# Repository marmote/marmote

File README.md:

Marmote is a National Science Foundation supported collaborative research project between Vanderbilt University and the University of Michigan. The goal of the project is to create a novel low-power experimental platform for wireless networking research and education.

The proposed Marmote platform breaks with the prevailing approach to wireless sensor network (WSN) hardware, which combines a general purpose microcontroller with a highly integrated radio transceiver, and places a flash-based Field Programmable Gate Array (FPGA) along with a flexible Analog Front-End (AFE) in the center to become:
 
 - low-power
 - powerful
 - flexible
 - modular
 
The above approach allows for interfacing and experimenting with different type of sensors including analog radio front-ends. In contrast with the "traditional" integrated radio chip solution this enables access to the physical layer and, hence, to baseband firmware development.

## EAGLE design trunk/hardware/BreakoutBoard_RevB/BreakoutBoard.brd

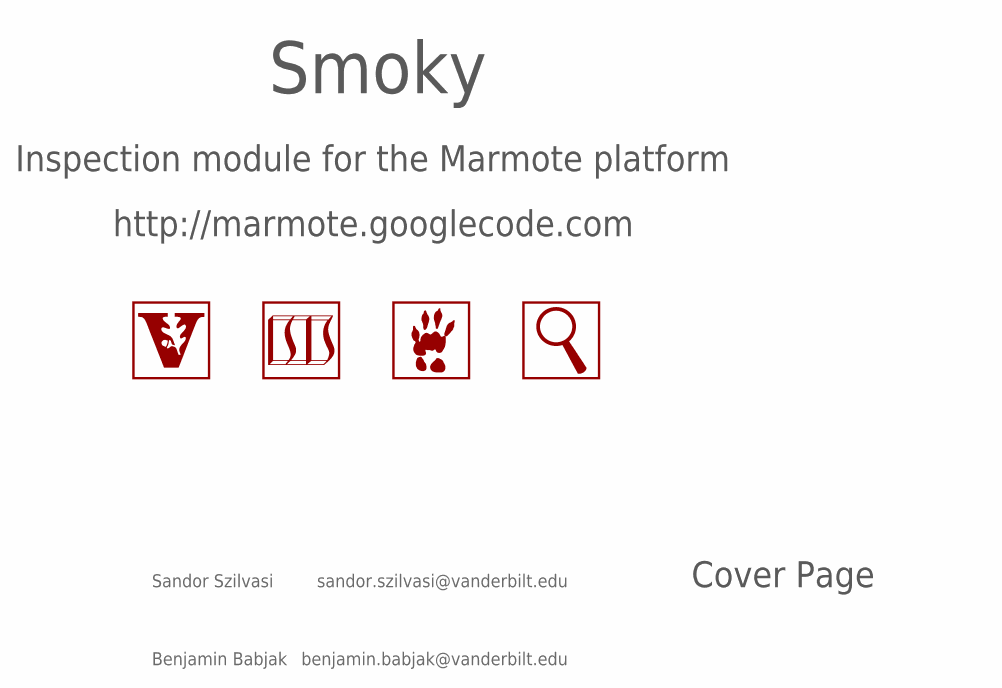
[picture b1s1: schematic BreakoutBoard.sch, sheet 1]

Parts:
LOGO1: LOGO-MAGNIFYING-GLASS-600MIL-10MM-SS; LOGO-MAGNIFYING-GLASS-10MM-SILKSCREEN
LOGO5: LOGO-VANDERBILT-600MIL-10MM-SS; LOGO-VANDERBILT-10MM-SILKSCREEN
LOGO6: LOGO-ISIS-600MIL-10MM-SS; LOGO-ISIS-10MM-SILKSCREEN
LOGO7: LOGO-MARMOTE-600MIL-10MM-SS; LOGO-MARMOTE-10MM-SILKSCREEN

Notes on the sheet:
Inspection module for the Marmote platform
http://marmote.googlecode.com

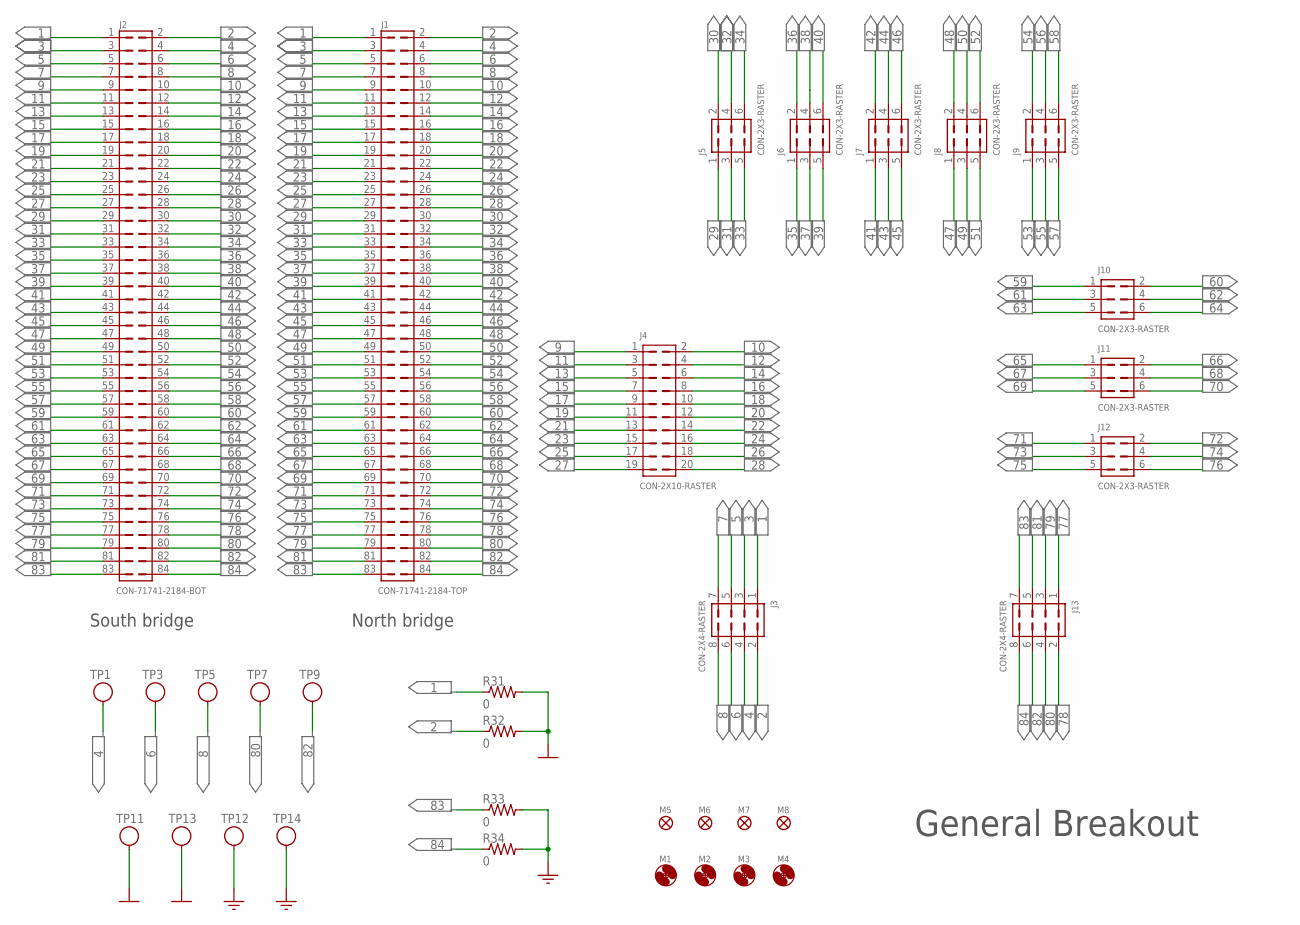
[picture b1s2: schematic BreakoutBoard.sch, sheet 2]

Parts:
J1: CON-71741-2184-TOP; 71741-0002
J2: CON-71741-2184-BOT; 71742-3003-BOT
J3, J13: CON-2X4-RASTER; 2X8
J4: CON-2X10-RASTER; 2X20
J5, J6, J7, J8, J9, J10, J11, J12: CON-2X3-RASTER; 2X6
M1, M2, M3, M4: MOUNT-HOLE3.3; 3,3
M5, M6, M7, M8: FIDUCIAL1X2; FIDUCIAL-1X2
R31, R32, R33, R34: 0; R0805
TP1, TP3, TP5: TESTPOINT-BLUE; TESTPOINT
TP7, TP9: TESTPOINT-GREEN; TESTPOINT
TP11, TP12, TP13, TP14: TESTPOINT-YELLOW; TESTPOINT

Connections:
1: J1.1, J2.1, J3.1, R31.1
2: J1.2, J2.2, J3.2, R32.1
3: J1.3, J2.3, J3.3
4: J1.4, J2.4, J3.4, TP1.1
5: J1.5, J2.5, J3.5
6: J1.6, J2.6, J3.6, TP3.1
7: J1.7, J2.7, J3.7
8: J1.8, J2.8, J3.8, TP5.1
9: J1.9, J2.9, J4.1
10: J1.10, J2.10, J4.2
11: J1.11, J2.11, J4.3
12: J1.12, J2.12, J4.4
13: J1.13, J2.13, J4.5
14: J1.14, J2.14, J4.6
15: J1.15, J2.15, J4.7
16: J1.16, J2.16, J4.8
17: J1.17, J2.17, J4.9
18: J1.18, J2.18, J4.10
19: J1.19, J2.19, J4.11
20: J1.20, J2.20, J4.12
21: J1.21, J2.21, J4.13
22: J1.22, J2.22, J4.14
23: J1.23, J2.23, J4.15
24: J1.24, J2.24, J4.16
25: J1.25, J2.25, J4.17
26: J1.26, J2.26, J4.18
27: J1.27, J2.27, J4.19
28: J1.28, J2.28, J4.20
29: J1.29, J2.29, J5.1
30: J1.30, J2.30, J5.2
31: J1.31, J2.31, J5.3
32: J1.32, J2.32, J5.4
33: J1.33, J2.33, J5.5
34: J1.34, J2.34, J5.6
35: J1.35, J2.35, J6.1
36: J1.36, J2.36, J6.2
37: J1.37, J2.37, J6.3
38: J1.38, J2.38, J6.4
39: J1.39, J2.39, J6.5
40: J1.40, J2.40, J6.6
41: J1.41, J2.41, J7.1
42: J1.42, J2.42, J7.2
43: J1.43, J2.43, J7.3
44: J1.44, J2.44, J7.4
45: J1.45, J2.45, J7.5
46: J1.46, J2.46, J7.6
47: J1.47, J2.47, J8.1
48: J1.48, J2.48, J8.2
49: J1.49, J2.49, J8.3
50: J1.50, J2.50, J8.4
51: J1.51, J2.51, J8.5
52: J1.52, J2.52, J8.6
53: J1.53, J2.53, J9.1
54: J1.54, J2.54, J9.2
55: J1.55, J2.55, J9.3
56: J1.56, J2.56, J9.4
57: J1.57, J2.57, J9.5
58: J1.58, J2.58, J9.6
59: J1.59, J2.59, J10.1
60: J1.60, J2.60, J10.2
61: J1.61, J2.61, J10.3
62: J1.62, J2.62, J10.4
63: J1.63, J2.63, J10.5
64: J1.64, J2.64, J10.6
65: J1.65, J2.65, J11.1
66: J1.66, J2.66, J11.2
67: J1.67, J2.67, J11.3
68: J1.68, J2.68, J11.4
69: J1.69, J2.69, J11.5
70: J1.70, J2.70, J11.6
71: J1.71, J2.71, J12.1
72: J1.72, J2.72, J12.2
73: J1.73, J2.73, J12.3
74: J1.74, J2.74, J12.4
75: J1.75, J2.75, J12.5
76: J1.76, J2.76, J12.6
77: J1.77, J2.77, J13.1
78: J1.78, J2.78, J13.2
79: J1.79, J2.79, J13.3
80: J1.80, J2.80, J13.4, TP7.1
81: J1.81, J2.81, J13.5
82: J1.82, J2.82, J13.6, TP9.1
83: J1.83, J2.83, J13.7, R33.1
84: J1.84, J2.84, J13.8, R34.1
AGND: R33.2, R34.2, TP12.1, TP14.1
DGND: R31.2, R32.2, TP11.1, TP13.1

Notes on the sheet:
South bridge
North bridge

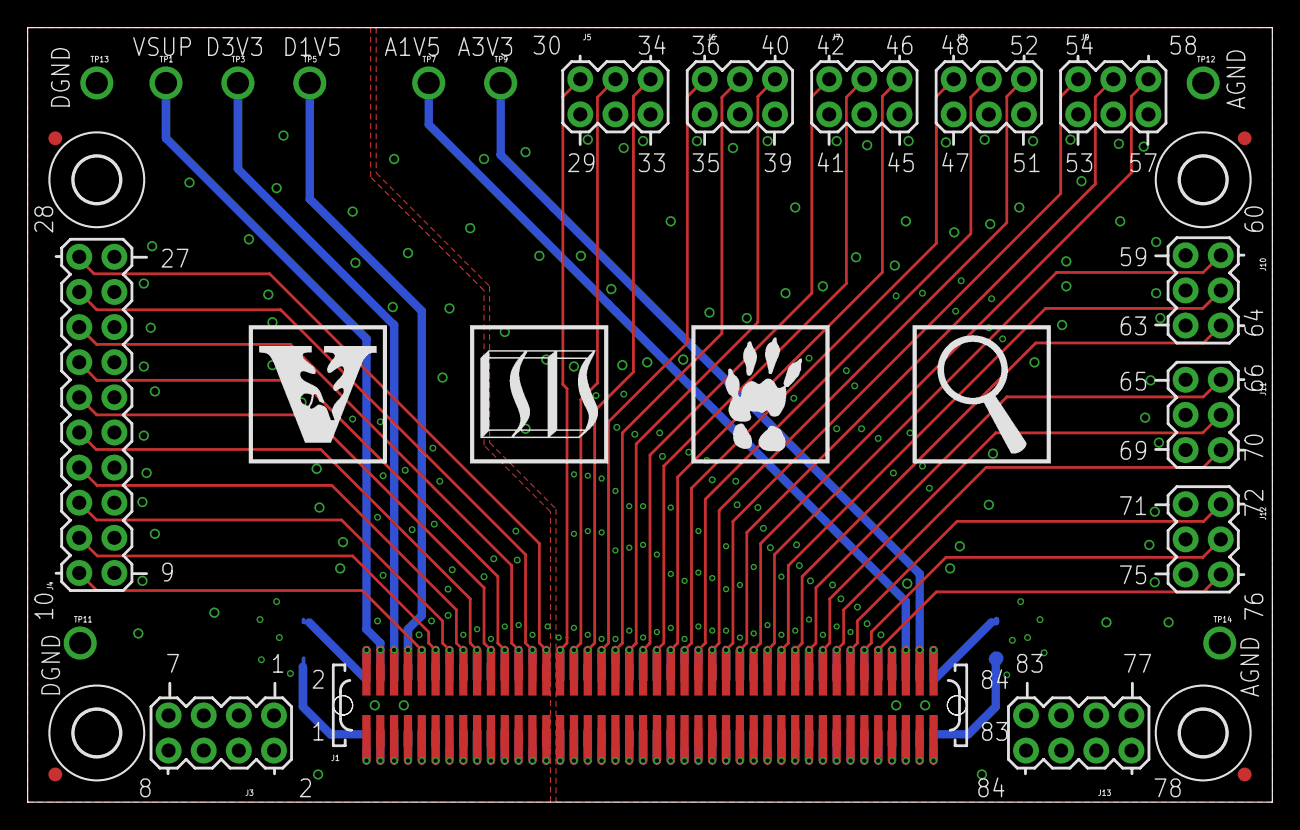
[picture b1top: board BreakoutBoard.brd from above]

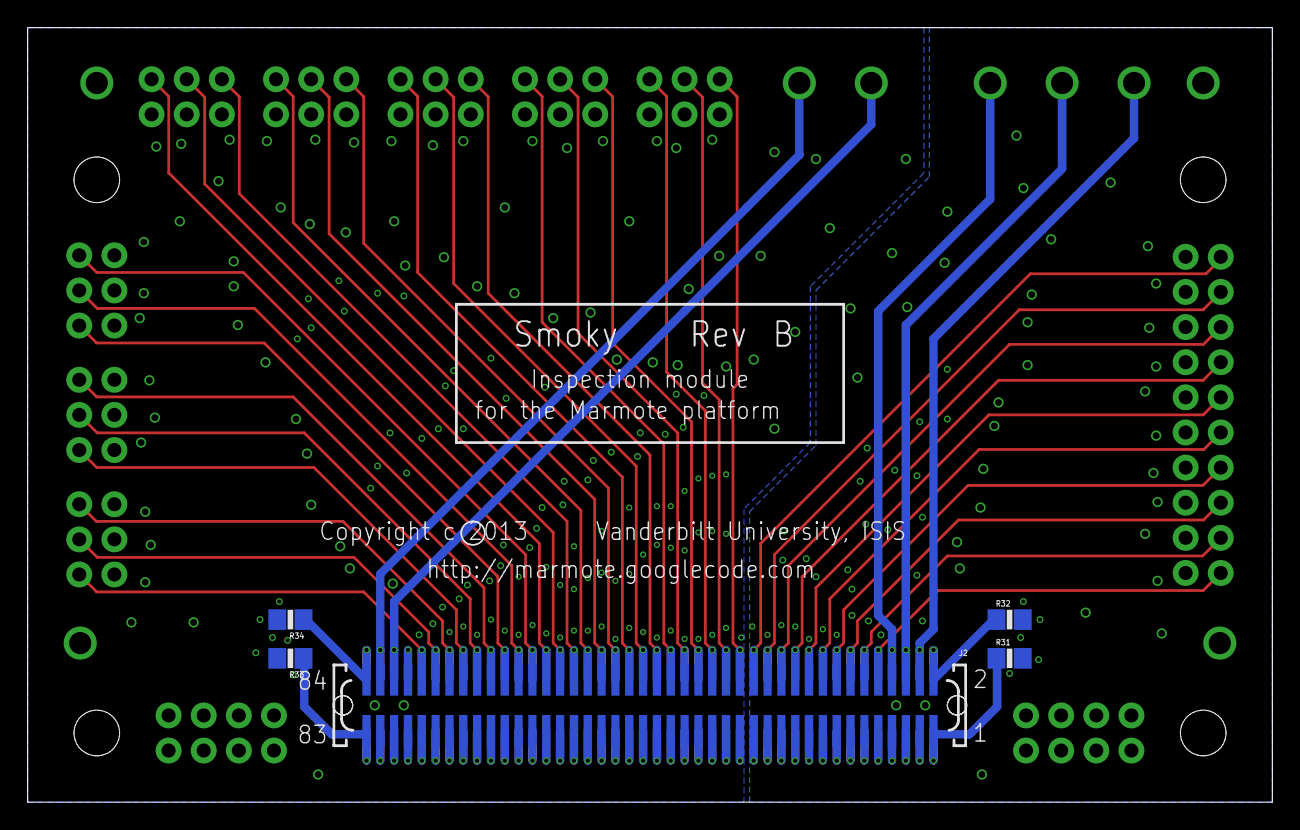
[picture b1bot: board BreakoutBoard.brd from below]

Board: 4 copper layers, 90.0 x 56.0 mm, 38 parts (5 on the bottom side), 86 nets.

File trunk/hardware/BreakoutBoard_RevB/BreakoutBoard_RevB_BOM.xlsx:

Bill of Materials for 'Marmote - Breakout Board Rev B (Smoky)'
Item # | Reference | Value | Package | Manufacturer | Manufacturer Part # | Supplier | Supplier Part # | Details | Qty | Unit Price | Total Cost
1 | J1 | CON-71741-2184-TOP | CON-71741-2184-TOP | Molex | 71741-0002 | Digi-Key | WM3498CT-ND | MEZZANINE 1MM BTB PLUG 84CKT | 1 | 6.24 | 6.24
2 | J2 | CON-71741-2184-BOT | CON-71741-2184-BOT | Molex | 71742-3003 | Digi-Key | WM3499CT-ND | MEZZANINE 1MM BTB RECPT 84CKT | 1 | 5.81 | 5.81
3 | J3, J4, J5, J6, J7, J8, J9, J10, J11, J12, J13* | CON-2X8 | CON-2X8 | Samtec | TSW-150-08-T-D-RA | Digi-Key | SAM1049-50-ND | CONN HEADR 100PS .100 DL R/A TIN | 1 | 4.62 | 4.62
4 | R31, R32, R33, R34 | 0 | R0805 | Rohm | MCR10EZHJ000 | Digi-Key | RHM0.0ACT-ND | RES 0.0 OHM 1/8W 0805 SMD | 4 | 4.1000000000000002E-2 | 0.16400000000000001
5 | TP1, TP3, TP5 | TESTPOINT | TESTPOINT-BLUE | Keystone | 5122 | Digi-Key | 5122K-ND | TEST POINT PC COMPACT T/H BLUE | 3 | 0.38 | 1.1400000000000001
6 | TP7, TP9 | TESTPOINT | TESTPOINT-GREEN | Keystone | 5121 | Digi-Key | 5121K-ND | TEST POINT PC COMPACT T/H GREEN | 2 | 0.38 | 0.76
7 | TP11, TP12, TP13, TP14 | TESTPOINT | TESTPOINT-YELLOW | Keystone | 5009 | Digi-Key | 5009K-ND | TEST POINT PC COMPACT .063"D YLW | 4 | 0.36 | 1.44
8 | Standoff | DNP | MOUNT-HOLE3.3 | Keystone | 7200 | Digi-Key | 7200K-ND | STANDOFF HEX M/F .375"L 4-40 BR | 4 | 0.68 | 2.72
 |  |  |  |  |  |  |  | Total | 20 |  | 22.894000000000005
*Note: The parts for J3, J4, ... J13 come from a single 2x50 header that needs 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

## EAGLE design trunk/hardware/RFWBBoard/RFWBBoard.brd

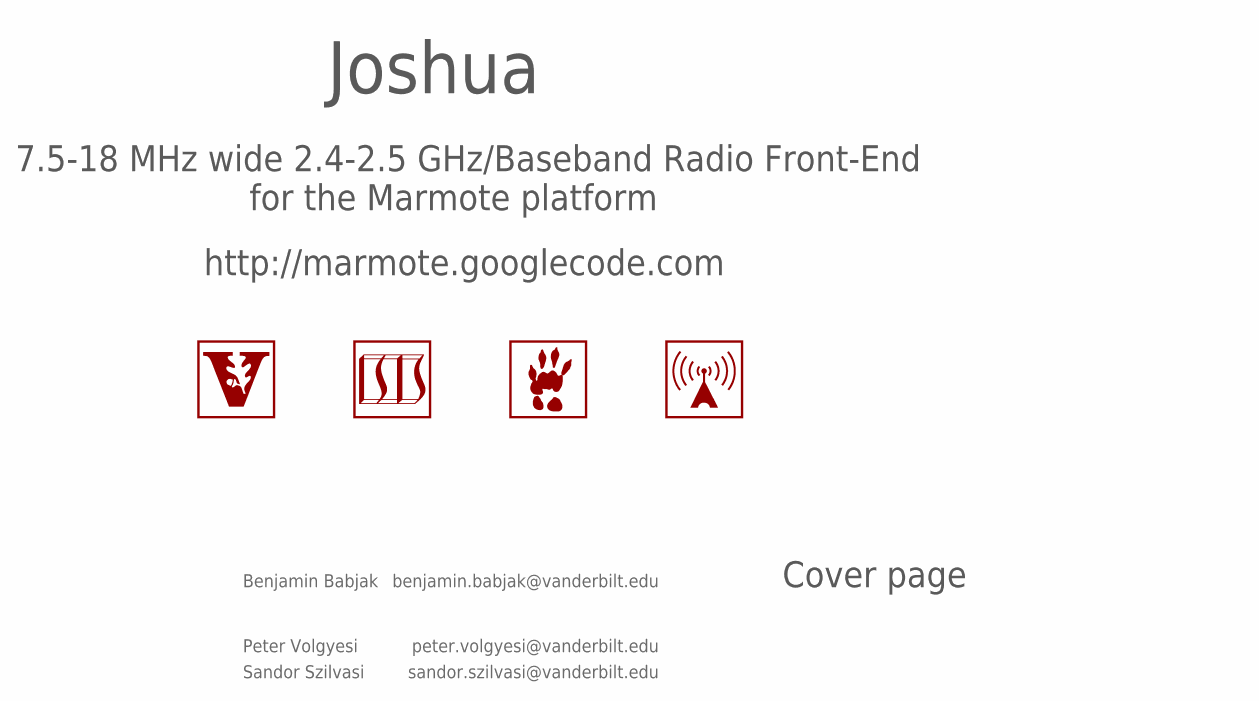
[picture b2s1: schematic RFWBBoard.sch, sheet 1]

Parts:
LOGO4: LOGO-ISIS-600MIL-10MM-SS; LOGO-ISIS-10MM-SILKSCREEN
LOGO5: LOGO-VANDERBILT-600MIL-10MM-SS; LOGO-VANDERBILT-10MM-SILKSCREEN
LOGO6: LOGO-MARMOTE-600MIL-10MM-SS; LOGO-MARMOTE-10MM-SILKSCREEN
LOGO7: LOGO-RADIO-3-600MIL-10MM-SS; LOGO-RADIO-FILLED-10MM-SILKSCREEN

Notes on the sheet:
7.5-18 MHz wide 2.4-2.5 GHz/Baseband Radio Front-End
http://marmote.googlecode.com
for the Marmote platform

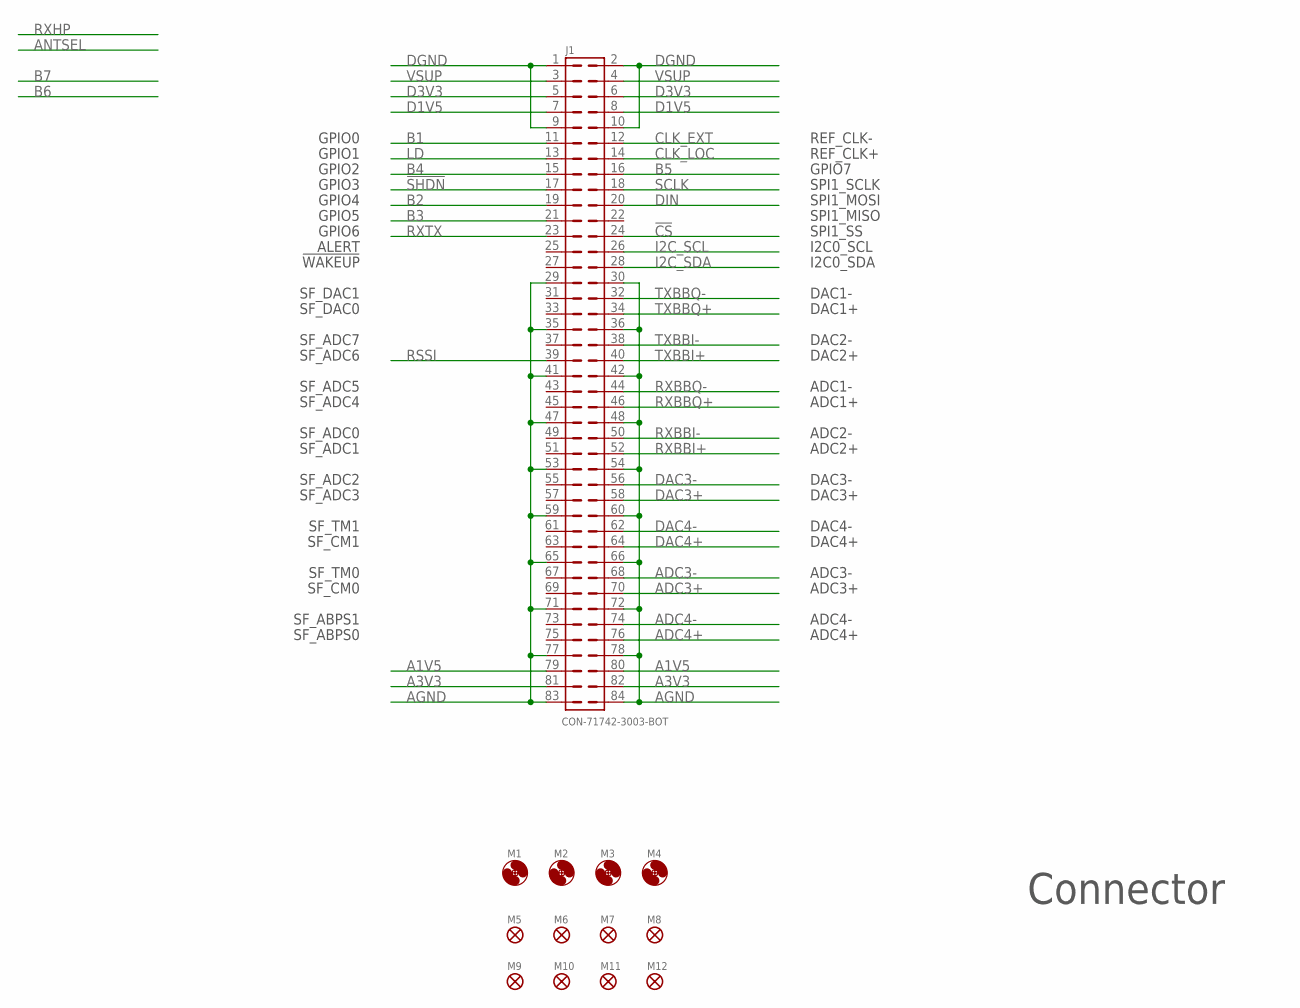
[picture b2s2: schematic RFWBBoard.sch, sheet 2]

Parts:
J1: CON-71742-3003-BOT; 71742-3003-BOT
M1, M2, M3, M4: MOUNT-HOLE3.3; 3,3
M5, M6, M7, M8, M9, M10, M11, M12: FIDUCIAL1X2; FIDUCIAL-1X2

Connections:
!CS: J1.24; also elsewhere on the board
!SHDN: J1.17; also elsewhere on the board
A1V5: J1.79, J1.80
A3V3: J1.81, J1.82; also elsewhere on the board
ADC3+: J1.70; also elsewhere on the board
ADC3-: J1.68; also elsewhere on the board
ADC4+: J1.76; also elsewhere on the board
ADC4-: J1.74; also elsewhere on the board
AGND: J1.29, J1.30, J1.35, J1.36, J1.41, J1.42, J1.47, J1.48, J1.53, J1.54, J1.59, J1.60, J1.65, J1.66, J1.71, J1.72, J1.77, J1.78, J1.83, J1.84; also elsewhere on the board
B1: J1.11; also elsewhere on the board
B2: J1.19; also elsewhere on the board
B3: J1.21; also elsewhere on the board
B4: J1.15; also elsewhere on the board
B5: J1.16; also elsewhere on the board
CLK_EXT: J1.12; also elsewhere on the board
CLK_LOC: J1.14; also elsewhere on the board
D1V5: J1.7, J1.8
D3V3: J1.5, J1.6; also elsewhere on the board
DAC3+: J1.58; also elsewhere on the board
DAC3-: J1.56; also elsewhere on the board
DAC4+: J1.64; also elsewhere on the board
DAC4-: J1.62; also elsewhere on the board
DGND: J1.1, J1.2, J1.9, J1.10; also elsewhere on the board
DIN: J1.20; also elsewhere on the board
I2C_SCL: J1.26; also elsewhere on the board
I2C_SDA: J1.28; also elsewhere on the board
LD: J1.13; also elsewhere on the board
RSSI: J1.39; also elsewhere on the board
RXBBI+: J1.52; also elsewhere on the board
RXBBI-: J1.50; also elsewhere on the board
RXBBQ+: J1.46; also elsewhere on the board
RXBBQ-: J1.44; also elsewhere on the board
RXTX: J1.23; also elsewhere on the board
SCLK: J1.18; also elsewhere on the board
TXBBI+: J1.40; also elsewhere on the board
TXBBI-: J1.38; also elsewhere on the board
TXBBQ+: J1.34; also elsewhere on the board
TXBBQ-: J1.32; also elsewhere on the board
VSUP: J1.3, J1.4

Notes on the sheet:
SF_ADC6
GPIO2
GPIO3
GPIO1
GPIO0
GPIO4
SPI1_SCLK
SPI1_MOSI
SPI1_MISO
SPI1_SS
I2C0_SCL
I2C0_SDA
DAC1-
DAC1+
DAC2-
DAC2+
ADC1-
ADC1+
ADC2-
ADC2+
DAC3-
DAC3+
DAC4-
DAC4+
ADC3-
ADC3+
ADC4-
ADC4+
REF_CLK-
REF_CLK+
GPIO5
ALERT
!WAKEUP
SF_ADC7
SF_DAC1
SF_DAC0
SF_ADC5
SF_ADC4
SF_ADC0
SF_ADC1

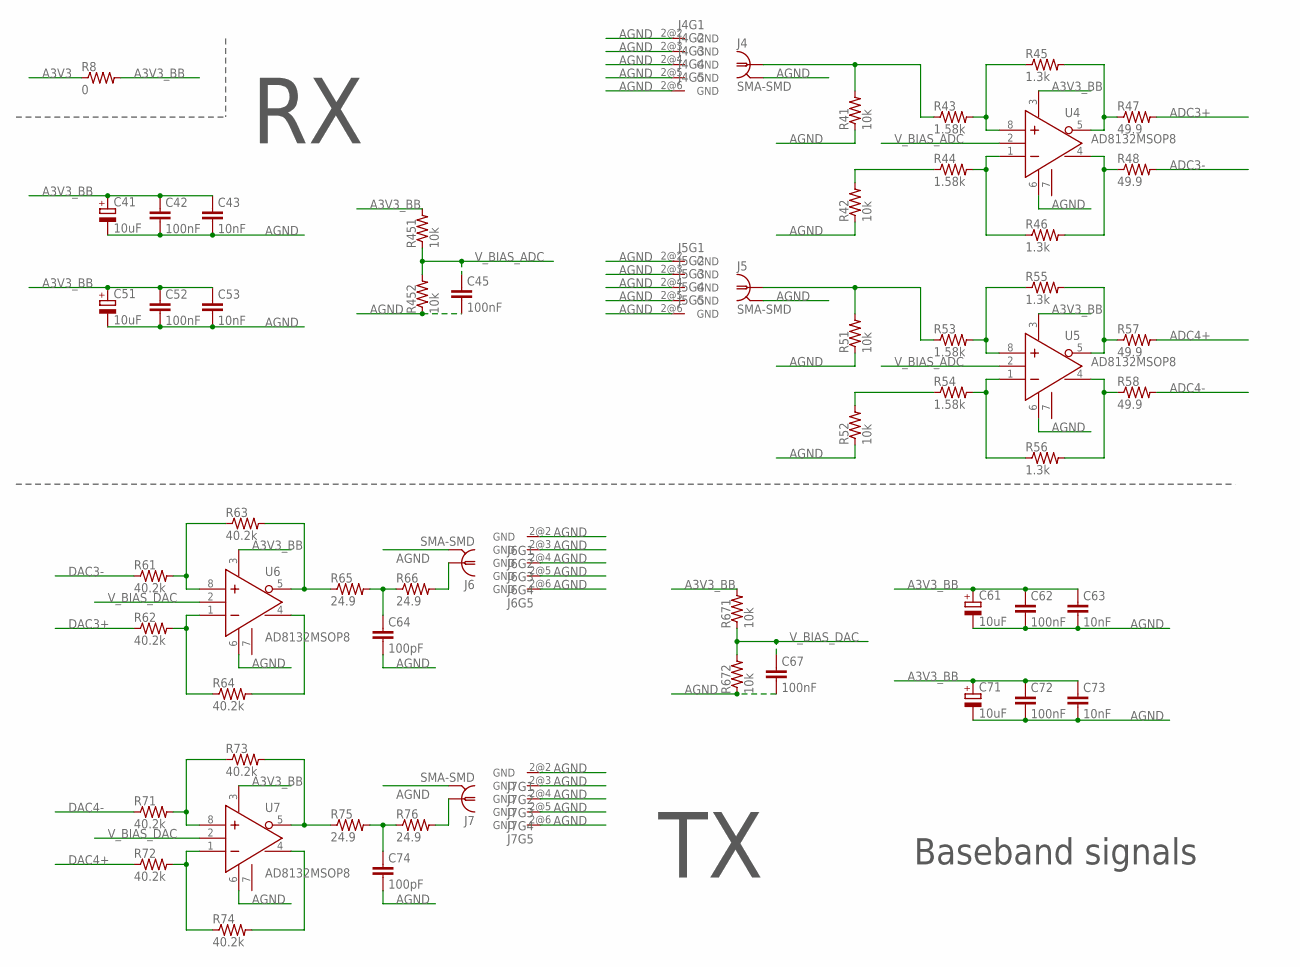
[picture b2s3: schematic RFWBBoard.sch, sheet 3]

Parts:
C41, C51, C61, C71: 10uF; CPOL2012
C42, C45, C52, C62, C67, C72: 100nF; C0402
C43, C53, C63, C73: 10nF; C0402
C64, C74: 100pF; C0402
J4, J5, J6, J7: SMA-SMD
R8: 0; R1206
R41, R42, R51, R52, R451, R452, R671, R672: 10k; R0402
R43, R44, R53, R54: 1.58k; R0402
R45, R46, R55, R56: 1.3k; R0402
R47, R48, R57, R58: 49.9; R0402
R61, R62, R63, R64, R71, R72, R73, R74: 40.2k; R0402
R65, R66, R75, R76: 24.9; R0402
U4, U5, U6, U7: AD8132MSOP8; MSOP8

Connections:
A3V3: R8.1; also elsewhere on the board
A3V3_BB: C41.+, C42.1, C43.1, C51.+, C52.1, C53.1, C61.+, C62.1, C63.1, C71.+, C72.1, C73.1, R8.2, R451.2, R671.2, U4.3 (V_S+), U5.3 (V_S+), U6.3 (V_S+), U7.3 (V_S+)
ADC3+: R47.2; also elsewhere on the board
ADC3-: R48.2; also elsewhere on the board
ADC4+: R57.2; also elsewhere on the board
ADC4-: R58.2; also elsewhere on the board
AGND: C41.-, C42.2, C43.2, C45.2, C51.-, C52.2, C53.2, C61.-, C62.2, C63.2, C64.2, C67.2, C71.-, C72.2, C73.2, C74.2, J4.2@1 (GND), J4.2@2 (GND), J4.2@3 (GND), J4.2@4 (GND), J4.2@5 (GND), J4.2@6 (GND), J5.2@1 (GND), J5.2@2 (GND), J5.2@3 (GND), J5.2@4 (GND), J5.2@5 (GND), J5.2@6 (GND), J6.2@1 (GND), J6.2@2 (GND), J6.2@3 (GND), J6.2@4 (GND), J6.2@5 (GND), J6.2@6 (GND), J7.2@1 (GND), J7.2@2 (GND), J7.2@3 (GND), J7.2@4 (GND), J7.2@5 (GND), J7.2@6 (GND), R41.1, R42.1, R51.1, R52.1, R452.1, R672.1, U4.6 (V_S-), U5.6 (V_S-), U6.6 (V_S-), U7.6 (V_S-); also elsewhere on the board
DAC3+: R62.1; also elsewhere on the board
DAC3-: R61.1; also elsewhere on the board
DAC4+: R72.1; also elsewhere on the board
DAC4-: R71.1; also elsewhere on the board
unnamed: J4.1, R41.2, R43.1
unnamed: R45.2, R47.1, U4.5 (-OUT)
unnamed: R46.2, R48.1, U4.4 (+OUT)
unnamed: R43.2, R45.1, U4.8 (+IN)
unnamed: R44.2, R46.1, U4.1 (-IN)
unnamed: J5.1, R51.2, R53.1
unnamed: R42.2, R44.1
unnamed: R55.2, R57.1, U5.5 (-OUT)
unnamed: R56.2, R58.1, U5.4 (+OUT)
unnamed: R53.2, R55.1, U5.8 (+IN)
unnamed: R54.2, R56.1, U5.1 (-IN)
unnamed: R52.2, R54.1
unnamed: R61.2, R63.1, U6.8 (+IN)
unnamed: R62.2, R64.1, U6.1 (-IN)
unnamed: R63.2, R65.1, U6.5 (-OUT)
unnamed: R64.2, U6.4 (+OUT)
unnamed: C64.1, R65.2, R66.1
unnamed: R71.2, R73.1, U7.8 (+IN)
unnamed: J6.1, R66.2
unnamed: R72.2, R74.1, U7.1 (-IN)
unnamed: R73.2, R75.1, U7.5 (-OUT)
unnamed: R74.2, U7.4 (+OUT)
unnamed: C74.1, R75.2, R76.1
unnamed: J7.1, R76.2
V_BIAS_ADC: C45.1, R451.1, R452.2, U4.2 (V_OCM), U5.2 (V_OCM)
V_BIAS_DAC: C67.1, R671.1, R672.2, U6.2 (V_OCM), U7.2 (V_OCM)

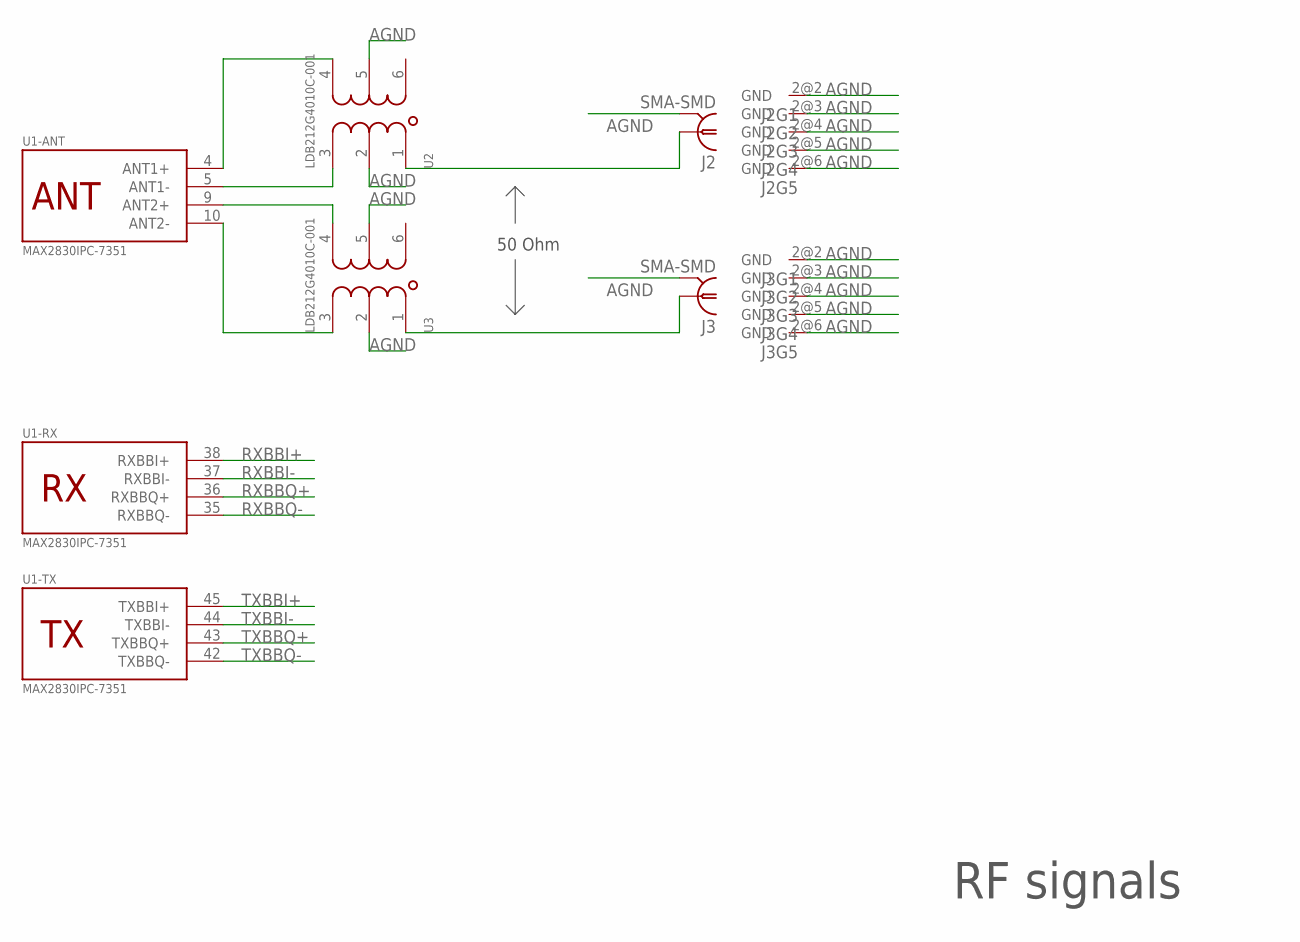
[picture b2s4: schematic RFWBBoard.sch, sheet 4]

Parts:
J2, J3: SMA-SMD
U1: MAX2830IPC-7351; TQFN-48
U2, U3: LDB212G4010C-001; LDB21-FOOTPRINT

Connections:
AGND: J2.2@1 (GND), J2.2@2 (GND), J2.2@3 (GND), J2.2@4 (GND), J2.2@5 (GND), J2.2@6 (GND), J3.2@1 (GND), J3.2@2 (GND), J3.2@3 (GND), J3.2@4 (GND), J3.2@5 (GND), J3.2@6 (GND), U2.2, U2.5, U3.2, U3.5; also elsewhere on the board
unnamed: U1.4 (ANT1+), U2.4
unnamed: U1.5 (ANT1-), U2.3
unnamed: U1.10 (ANT2-), U3.3
unnamed: U1.9 (ANT2+), U3.4
unnamed: J2.1, U2.1
unnamed: J3.1, U3.1
RXBBI+: U1.38 (RXBBI+); also elsewhere on the board
RXBBI-: U1.37 (RXBBI-); also elsewhere on the board
RXBBQ+: U1.36 (RXBBQ+); also elsewhere on the board
RXBBQ-: U1.35 (RXBBQ-); also elsewhere on the board
TXBBI+: U1.45 (TXBBI+); also elsewhere on the board
TXBBI-: U1.44 (TXBBI-); also elsewhere on the board
TXBBQ+: U1.43 (TXBBQ+); also elsewhere on the board
TXBBQ-: U1.42 (TXBBQ-); also elsewhere on the board

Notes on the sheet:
50 Ohm

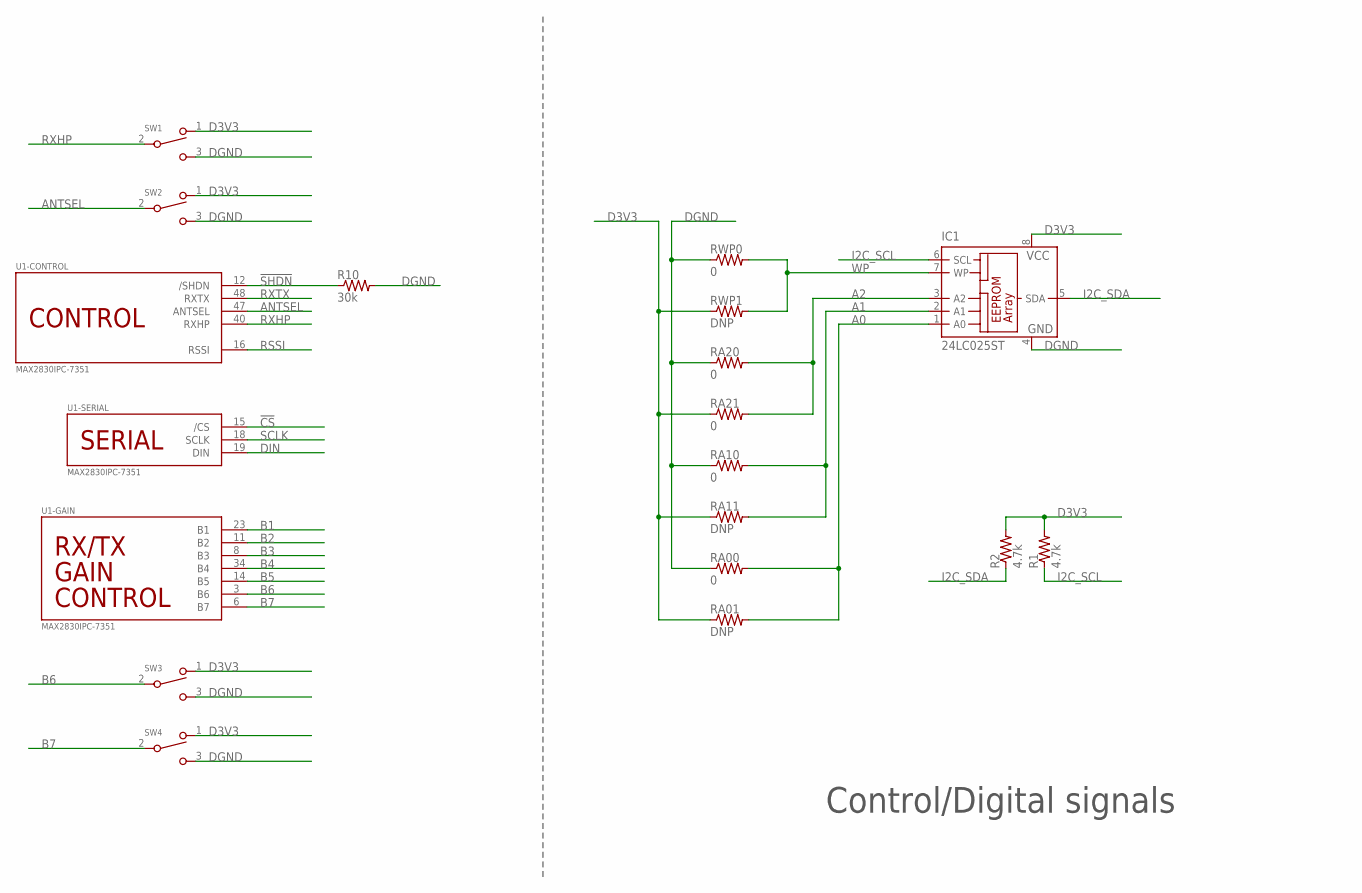
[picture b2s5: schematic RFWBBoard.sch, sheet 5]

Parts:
IC1: 24LC025ST; TSSOP8
R1, R2: 4.7k; R0402
R10: 30k; R0402
RA00, RA10, RA20, RA21: 0; R0402
RA01, RA11: DNP; R0402
RWP0: 0; R0402
RWP1: DNP; R0402
SW1, SW2, SW3, SW4: SWITCH-CJS-1200TA; SWITCH-DIP-CJS
U1: MAX2830IPC-7351; TQFN-48

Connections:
!CS: U1.15 (/CS); also elsewhere on the board
!SHDN: R10.1, U1.12 (/SHDN); also elsewhere on the board
A0: IC1.1 (A0), RA00.2, RA01.2
A1: IC1.2 (A1), RA10.2, RA11.2
A2: IC1.3 (A2), RA20.2, RA21.2
ANTSEL: SW2.2, U1.47 (ANTSEL)
B1: U1.23 (B1); also elsewhere on the board
B2: U1.11 (B2); also elsewhere on the board
B3: U1.8 (B3); also elsewhere on the board
B4: U1.34 (B4); also elsewhere on the board
B5: U1.14 (B5); also elsewhere on the board
B6: SW3.2, U1.3 (B6)
B7: SW4.2, U1.6 (B7)
D3V3: IC1.8 (VCC), R1.2, R2.2, RA01.1, RA11.1, RA21.1, RWP1.1, SW1.1, SW2.1, SW3.1, SW4.1; also elsewhere on the board
DGND: IC1.4 (GND), R10.2, RA00.1, RA10.1, RA20.1, RWP0.1, SW1.3, SW2.3, SW3.3, SW4.3; also elsewhere on the board
DIN: U1.19 (DIN); also elsewhere on the board
I2C_SCL: IC1.6 (SCL), R1.1; also elsewhere on the board
I2C_SDA: IC1.5 (SDA), R2.1; also elsewhere on the board
RSSI: U1.16 (RSSI); also elsewhere on the board
RXHP: SW1.2, U1.40 (RXHP)
RXTX: U1.48 (RXTX); also elsewhere on the board
SCLK: U1.18 (SCLK); also elsewhere on the board
WP: IC1.7 (WP), RWP0.2, RWP1.2

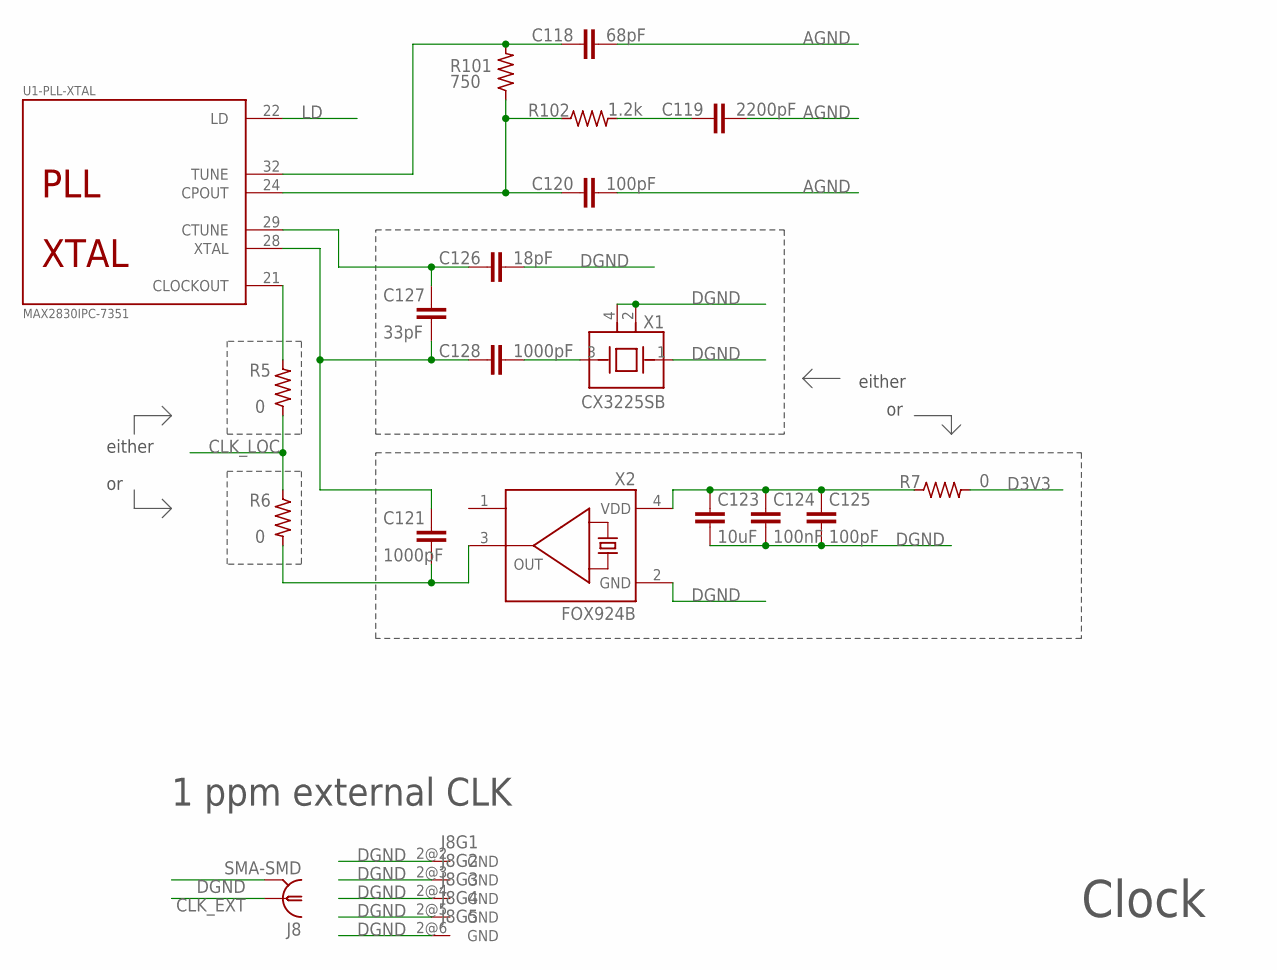
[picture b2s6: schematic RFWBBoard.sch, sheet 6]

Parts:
C118: 68pF; C0402
C119: 2200pF; C0402
C120, C125: 100pF; C0402
C121, C128: 1000pF; C0402
C123: 10uF; C0805
C124: 100nF; C0402
C126: 18pF; C0402
C127: 33pF; C0402
J8: SMA-SMD
R5, R6: 0; R0402
R7: 0; R1206
R101: 750; R0402
R102: 1.2k; R0402
U1: MAX2830IPC-7351; TQFN-48
X1: CX3225SB
X2: FOX924B; FOX924

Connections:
AGND: C118.2, C119.2, C120.2; also elsewhere on the board
CLK_EXT: J8.1; also elsewhere on the board
CLK_LOC: R5.1, R6.1; also elsewhere on the board
D3V3: R7.2; also elsewhere on the board
DGND: C123.2, C124.2, C125.2, C126.1, J8.2@1 (GND), J8.2@2 (GND), J8.2@3 (GND), J8.2@4 (GND), J8.2@5 (GND), J8.2@6 (GND), X1.1, X1.2, X1.4, X2.2 (GND); also elsewhere on the board
LD: U1.22 (LD); also elsewhere on the board
unnamed: C118.1, R101.2, U1.32 (TUNE)
unnamed: C121.1, C127.2, C128.2, U1.28 (XTAL)
unnamed: C119.1, R102.2
unnamed: C120.1, R101.1, R102.1, U1.24 (CPOUT)
unnamed: C121.2, R6.2, X2.3 (FO)
unnamed: C123.1, C124.1, C125.1, R7.1, X2.4 (VCC)
unnamed: R5.2, U1.21 (CLOCKOUT)
unnamed: C128.1, X1.3
unnamed: C126.2, C127.1, U1.29 (CTUNE)

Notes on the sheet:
either
1 ppm external CLK

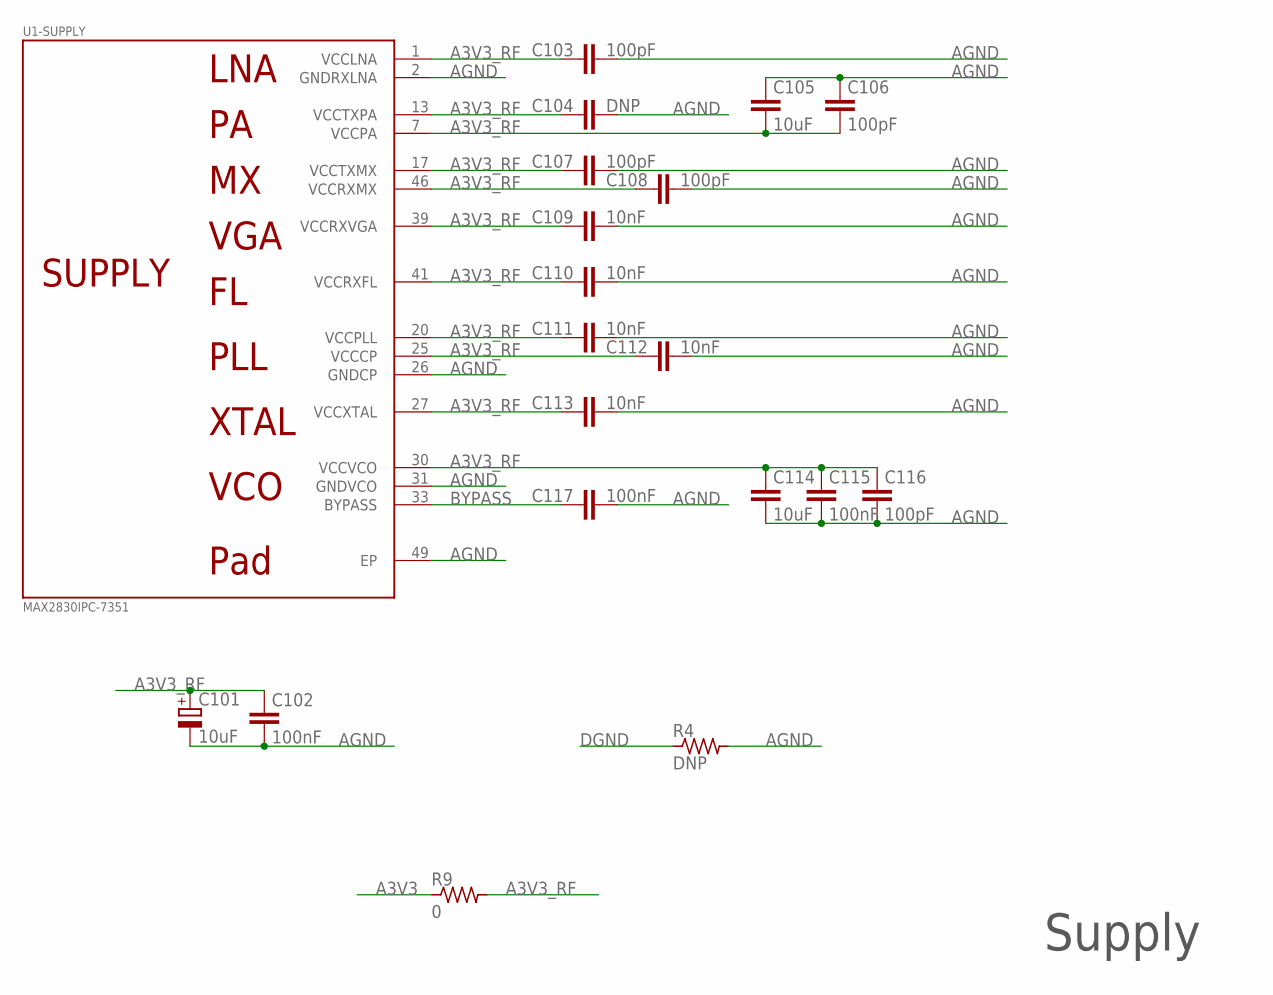
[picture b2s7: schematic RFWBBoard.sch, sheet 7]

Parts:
C101: 10uF; CPOL2012
C102, C115, C117: 100nF; C0402
C103, C106, C107, C108, C116: 100pF; C0402
C104: DNP; C0402
C105: 10uF; C1206
C109, C110, C111, C112, C113: 10nF; C0402
C114: 10uF; C0805
R4: DNP; R1206
R9: 0; R1206
U1: MAX2830IPC-7351; TQFN-48

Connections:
A3V3: R9.1; also elsewhere on the board
A3V3_RF: C101.+, C102.1, C103.1, C104.1, C105.2, C106.2, C107.1, C108.1, C109.1, C110.1, C111.1, C112.1, C113.1, C114.1, C115.1, C116.1, R9.2, U1.1 (VCCLNA), U1.7 (VCCPA), U1.13 (VCCTXPA), U1.17 (VCCTXMX), U1.20 (VCCPLL), U1.25 (VCCCP), U1.27 (VCCXTAL), U1.30 (VCCVCO), U1.39 (VCCRXVGA), U1.41 (VCCRXFL), U1.46 (VCCRXMX)
AGND: C101.-, C102.2, C103.2, C104.2, C105.1, C106.1, C107.2, C108.2, C109.2, C110.2, C111.2, C112.2, C113.2, C114.2, C115.2, C116.2, C117.2, R4.2, U1.2 (GNDRXLNA), U1.26 (GNDCP), U1.31 (GNDVCO), U1.49 (EP); also elsewhere on the board
BYPASS: C117.1, U1.33 (BYPASS)
DGND: R4.1; also elsewhere on the board

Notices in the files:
hardware/BreakoutBoard/BreakoutBoard.sch:
COPYRIGHT: Copyright © 2011 Vanderbilt University, ISIS
hardware/PowerBoard/PowerBoard.sch:
COPYRIGHT: Copyright © 2013 Vanderbilt University, ISIS
parts and their libraries:
BreakoutBoard: Copyright © 2012 Vanderbilt University, ISIS
powerboard: Copyright © 2011 Vanderbilt University, ISIS
MainBoard: Copyright © 2013 Vanderbilt University, ISIS
